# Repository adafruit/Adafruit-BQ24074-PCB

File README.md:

## Adafruit BQ24074 Solar Charger PCB

<a href="https://www.adafruit.com/product/4755"><br/>
Click here to purchase one from the Adafruit shop</a>

PCB files for the Adafruit BQ24074 Solar Charger. 

Format is EagleCAD schematic and board layout
* https://www.adafruit.com/product/4755

### Description

This charger is the only one you need to keep all your Lithium Polymer (LiPoly) or Lithium Ion (LiIon) rechargeable batteries topped up. No matter the power source at your disposal! The Adafruit Universal USB / DC / Solar Lithium Ion/Polymer Charger can use USB, DC or Solar power, with a wide 5-10V input voltage range! The charger chip is super smart, and will reduce the current draw if the input voltage starts to dip under 4.5V, making it a perfect near-MPPT solar charger that you can use with a wide range of panels.

### License

Adafruit invests time and resources providing this open source design, please support Adafruit and open-source hardware by purchasing products from [Adafruit](https://www.adafruit.com)!

Designed by Limor Fried/Ladyada for Adafruit Industries.

Creative Commons Attribution/Share-Alike, all text above must be included in any redistribution. 
See license.txt for additional details.

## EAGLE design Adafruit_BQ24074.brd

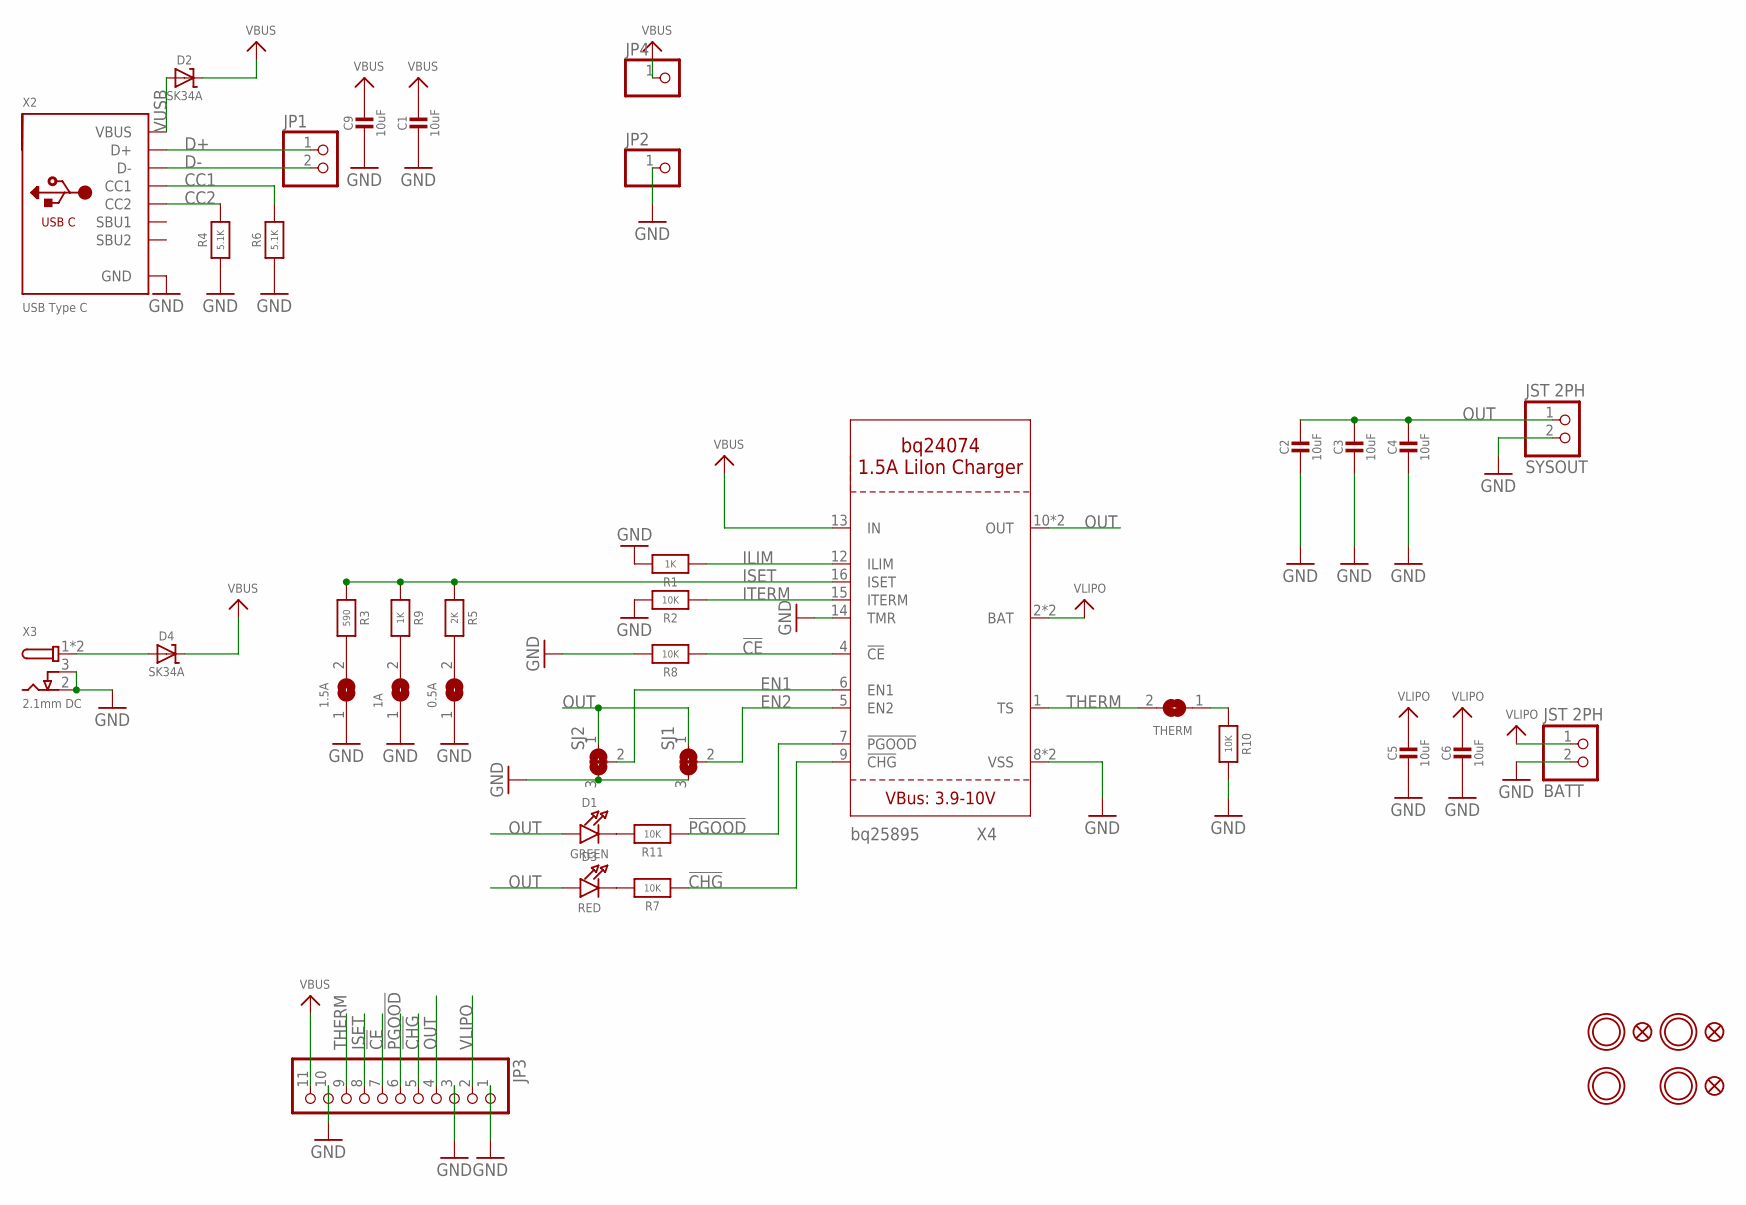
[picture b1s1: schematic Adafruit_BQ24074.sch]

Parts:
0.5A, 1.5A: SOLDERJUMPER; SOLDERJUMPER_ARROW_NOPASTE
1A: SOLDERJUMPERCLOSED; SOLDERJUMPER_CLOSEDWIRE
BATT: JST 2PH; JST-PH-2-SMT-RA
C1, C2, C3, C4, C5, C6, C9: 10uF; 0805-NO
D1: GREEN; CHIPLED_0603
D2, D4: SK34A; SMADIODE
D3: RED; CHIPLED_0603
FID1, FID2, FID3: FIDUCIAL_1MM
JP1: HEADER-1X2ROUND; 1X02_ROUND
JP2, JP4: HEADER-1X1; 1X01_OVAL
JP3: HEADER-1X1176MIL; 1X11_ROUND_76
R1, R9: 1K; 0603-NO
R2, R7, R8, R10, R11: 10K; 0603-NO
R3: 590; 0603-NO
R4, R6: 5.1K; 0603-NO
R5: 2K; 0603-NO
SJ1, SJ2: SOLDERJUMPER_2WAY; SOLDERJUMPER_2WAY_OPEN_NOPASTE
SYSOUT: JST 2PH; JST-PH-2-SMT-RA
THERM: SOLDERJUMPERCLOSED; SOLDERJUMPER_CLOSEDWIRE
U$3, U$4, U$11, U$12: MOUNTINGHOLE2.5; MOUNTINGHOLE_2.5_PLATED
X2: USB Type C; USB_C_CUSB31-CFM2AX-01-X
X3: 2.1mm DC; DCJACK_2MM_SMT
X4: BQ24074; QFN16_3MM

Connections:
!CE: JP3.7, R8.1, X4.4 (!CE)
!CHG: JP3.5, R7.1, X4.9 (!CHG)
!PGOOD: JP3.6, R11.1, X4.7 (!PGOOD)
CC1: R6.2, X2.A5 (CC1)
CC2: R4.2, X2.B5 (CC2)
D+: JP1.1, X2.A6 (D+), X2.B6 (D+)
D-: JP1.2, X2.A7 (D-), X2.B7 (D-)
EN1: SJ2.2, X4.6 (EN1)
EN2: SJ1.2, X4.5 (EN2)
GND: 0.5A.1, 1.5A.1, 1A.1, BATT.2 (1), C1.2, C2.2, C3.2, C4.2, C5.2, C6.2, C9.2, JP2.1, JP3.1, JP3.3, JP3.10, R1.2, R2.2, R4.1, R6.1, R8.2, R10.2, SJ1.3, SJ2.3, SYSOUT.2 (1), X2.A1B12 (GND), X2.B1A12 (GND), X3.2 (GND), X3.3 (GNDBREAK), X4.8 (VSS), X4.14 (TMR), X4.THERMAL (VSS)
ILIM: R1.1, X4.12 (ILIM)
ISET: JP3.8, R3.1, R5.1, R9.1, X4.16 (ISET)
ITERM: R2.1, X4.15 (ITERM)
unnamed: D1.C, R11.2
unnamed: D4.A, X3.1 (PWR), X3.1' (PWR)
unnamed: D3.C, R7.2
unnamed: 1.5A.2, R3.2
unnamed: 0.5A.2, R5.2
unnamed: 1A.2, R9.2
unnamed: R10.1, THERM.1
OUT: C2.1, C3.1, C4.1, D1.A, D3.A, JP3.4, SJ1.1, SJ2.1, SYSOUT.1 (2), X4.10 (OUT), X4.11 (OUT)
THERM: JP3.9, THERM.2, X4.1 (TS)
VBUS: C1.1, C9.1, D2.C, D4.C, JP3.11, JP4.1, X4.13 (IN)
VLIPO: BATT.1 (2), C5.1, C6.1, JP3.2, X4.2 (BAT), X4.3 (BAT)
VUSB: D2.A, X2.A4B9 (VBUS), X2.B4A9 (VBUS)

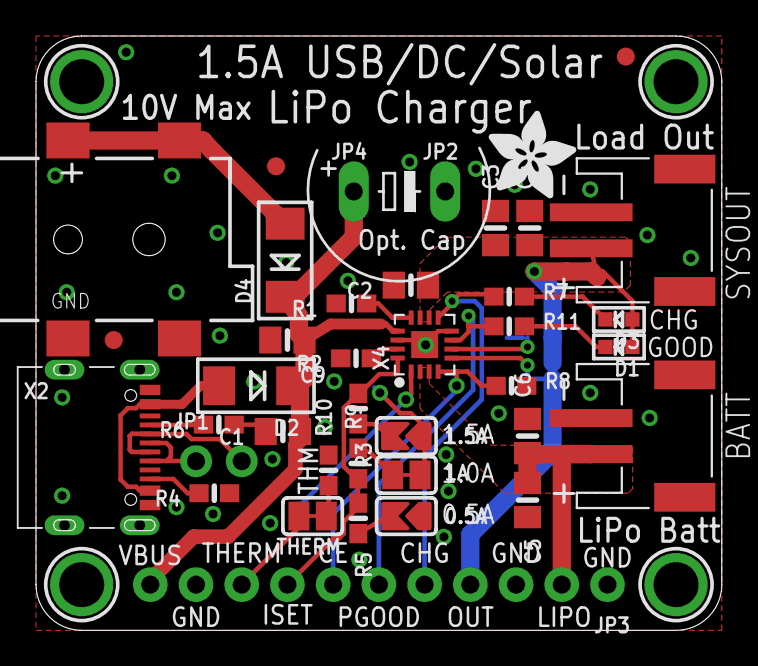
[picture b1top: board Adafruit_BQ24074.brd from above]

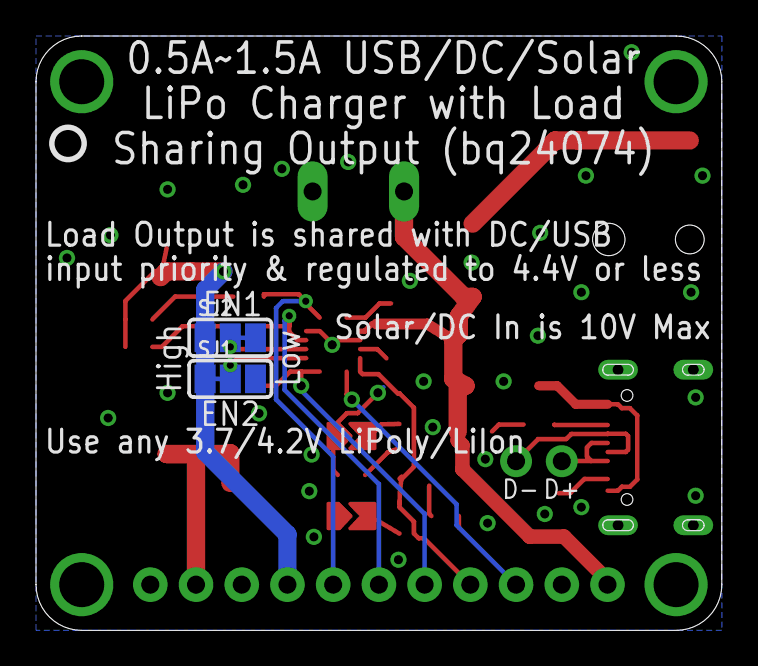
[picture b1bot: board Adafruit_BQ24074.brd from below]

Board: 2 copper layers, 38.1 x 33.0 mm, 46 parts (3 on the bottom side), 25 nets.

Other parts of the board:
U$14: ADAFRUIT_5MM
U$18: PCBFEAT-REV-040

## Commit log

2020-09-15 updating dims and image
2021-05-19 Fixed dead link in README.md
2021-05-19 Added description to README.md
